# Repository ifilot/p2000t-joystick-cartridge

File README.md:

# P2000T Joystick Cartridge for SLOT2

This cartridge enables the use of Atari 2600-style joysticks with the P2000T by
emulating keyboard inputs. It uses an EEPROM and a few logic chips to translate
joystick button presses into keystrokes, seamlessly integrating with the
P2000T's keyboard polling process.

> [!TIP]
> Download a copy of the EEPROM binary [via this link](https://github.com/ifilot/p2000t-joystick-cartridge/releases/download/nightly/joystick_eeprom.bin).

## PCB

## Working

The P2000T features a matrix keyboard design, where each key is positioned at the intersection of a specific row and column. The rows are connected to the address pins, while the columns are connected to the data pins. The keyboard matrix consists of 10 rows and 8 columns.

## Keyboard Polling Process

To poll the keyboard, the P2000T employs a two-step process:

1. **Initialize Rows**: The P2000T writes a `1` to the `BIT6` position of I/O
   port `0x10`, which ties all rows to ground (GND).
2. **Detect Key Presses**: The P2000T then reads from I/O port `0x00`. If at
   least one key is pressed, the read value will differ from `0xFF`.

If a key press is detected, the P2000T proceeds with an additional step:

3. **Detect specific key**: Each row is sequentially pulled down by reading from
   I/O ports `0x00` to `0x0A`. A zero-bit received during any of these read
   operations indicates the presence of a key press. The corresponding key is
   mapped to a specific keystroke based on its position in the matrix.

The described process is emulated using a single EEPROM and a few logic chips.
The EEPROM’s address pins are connected to both the joystick buttons and the
lower address bus used by the P2000T during the keyboard polling process. To
detect the polling of the lines, a 74HC138 decoder is used. This decoder latches
the D6 pin to capture the first phase of the keyboard polling process. During
this phase, if any joystick button is pressed, the EEPROM generates the same
output as if a key on the keyboard had been pressed. In the second phase, the
EEPROM continues the emulation process. However, it now produces the output
precisely when the corresponding row in the keyboard matrix is pulled low.

The use of an EEPROM makes this process fully programmable, allowing the user to
create any desired joystick-to-keyboard mapping. With 10 joystick buttons (5 per
joystick across 2 ports), only 32 KiB of EEPROM memory is required to store the
mappings. Since even the smallest SST39SF0x0-type EEPROM has a capacity of 128
KiB, a single chip can accommodate up to four different joystick/keyboard
mappings. To enable users to select their preferred mapping, a DIP switch is
included, allowing easy switching between the stored configurations.

### Schematic

[Download schematic](pcb/p2000t-joystick-slot2-eeprom/p2000t-joystick-slot2-eeprom.pdf)

## Programming the EEPROM

To generate the data for the EEPROM, you can use [this
script](scripts/eeprom.py). The data can be written to the EEPROM using, for
example, [this hardware solution](https://github.com/ifilot/pico-sst39sf0x0-programmer).

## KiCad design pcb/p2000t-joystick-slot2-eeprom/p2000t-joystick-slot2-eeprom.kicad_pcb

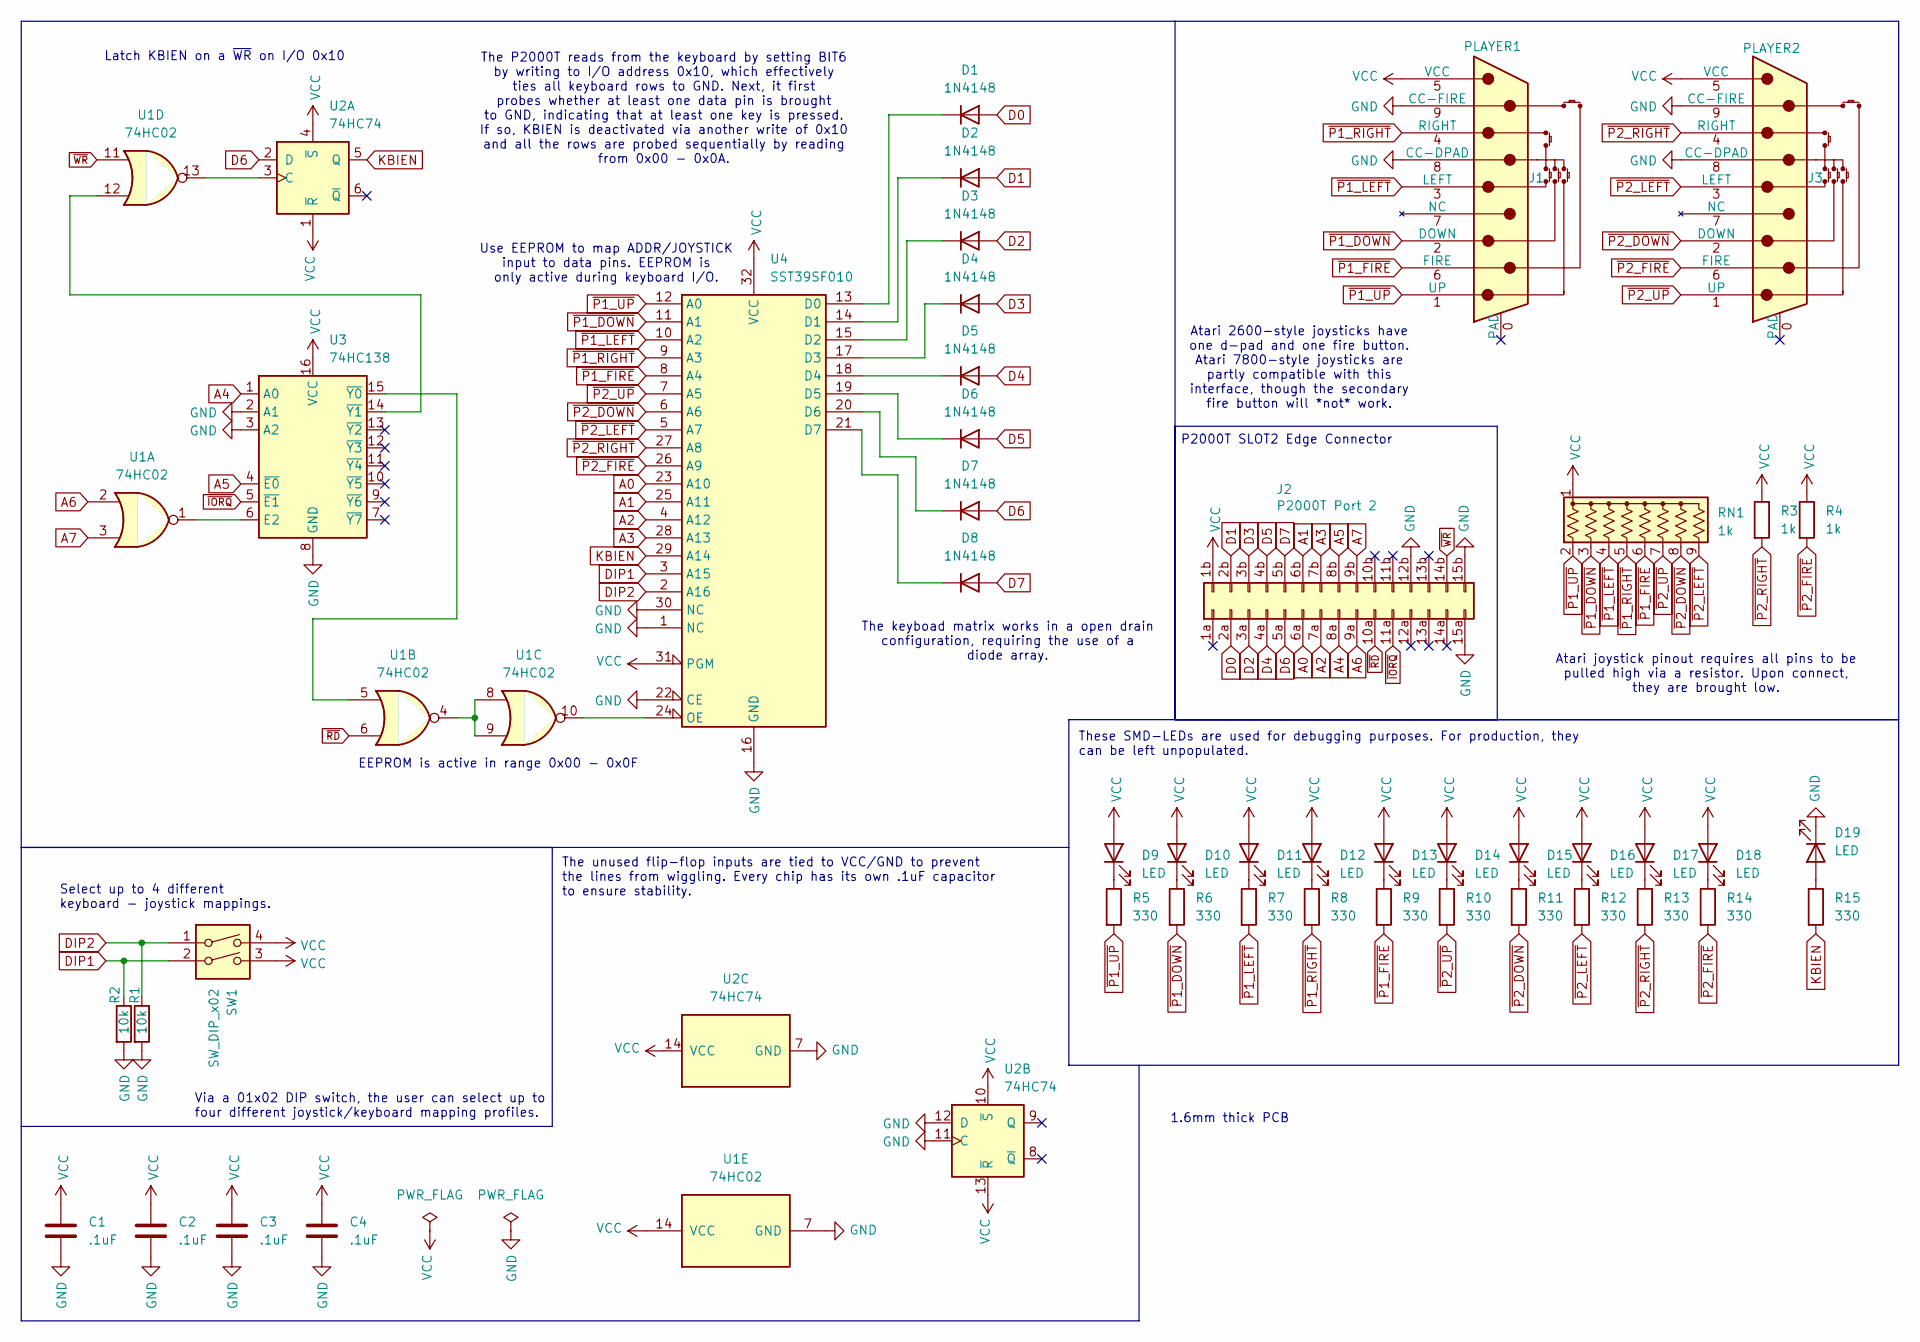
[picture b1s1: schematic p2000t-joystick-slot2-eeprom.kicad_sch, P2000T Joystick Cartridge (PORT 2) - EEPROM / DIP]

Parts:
C1, C2, C3, C4: .1uF; C_Disc_D5.0mm_W2.5mm_P5.00mm
D1, D2, D3, D4, D5, D6, D7, D8: 1N4148; D_DO-35_SOD27_P7.62mm_Horizontal
D9, D10, D11, D12, D13, D14, D15, D16, D17, D18, D19: LED; LED_0805_2012Metric_Pad1.15x1.40mm_HandSolder
J1: PLAYER1; DSUB-9_Male_Horizontal_P2.77x2.84mm_EdgePinOffset4.94mm_Hou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
J2: P2000T Port 2; p2000t_cartridge_edge
J3: PLAYER2; DSUB-9_Male_Horizontal_P2.77x2.84mm_EdgePinOffset4.94mm_Hou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
R1, R2: 10k; R_Axial_DIN0207_L6.3mm_D2.5mm_P7.62mm_Horizontal
R3, R4: 1k; R_Axial_DIN0207_L6.3mm_D2.5mm_P7.62mm_Horizontal
R5, R6, R7, R8, R9, R10, R11, R12, R13, R14, R15: 330; R_0805_2012Metric_Pad1.20x1.40mm_HandSolder
RN1: 1k; R_Array_SIP9
SW1: SW_DIP_x02; SW_DIP_SPSTx02_Slide_9.78x7.26mm_W7.62mm_P2.54mm
U1: 74HC02; DIP-14_W7.62mm_Socket
U2: 74HC74; DIP-14_W7.62mm_Socket
U3: 74HC138; DIP-16_W7.62mm_Socket
U4: SST39SF010; PLCC-32_THT-Socket

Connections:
A0: J2.6a, U4.23 (A10)
A1: J2.6b, U4.25 (A11)
A2: J2.7a, U4.4 (A12)
A3: J2.7b, U4.28 (A13)
A4: J2.8a, U3.1 (A0)
A5: J2.8b, U3.4 (~E0)
A6: J2.9a, U1.2
A7: J2.9b, U1.3
D0: D1.2 (A), J2.2a
D1: D2.2 (A), J2.2b
D2: D3.2 (A), J2.3a
D3: D4.2 (A), J2.3b
D4: D5.2 (A), J2.4a
D5: D6.2 (A), J2.4b
D6: D7.2 (A), J2.5a, U2.2 (D)
D7: D8.2 (A), J2.5b
DIP1: R2.1, SW1.2, U4.3 (A15)
DIP2: R1.1, SW1.1, U4.2 (A16)
GND: C1.2, C2.2, C3.2, C4.2, D19.1 (K), J1.8 (CC-DPAD), J1.9 (CC-FIRE), J2.12b, J2.15a, J2.15b, J3.8 (CC-DPAD), J3.9 (CC-FIRE), R1.2, R2.2, U1.7 (GND), U2.7 (GND), U2.11 (C), U2.12 (D), U3.2 (A1), U3.3 (A2), U3.8 (GND), U4.1 (NC), U4.16 (GND), U4.22 (CE), U4.30 (NC)
KBIEN: R15.2, U2.5 (Q), U4.29 (A14)
unnamed: D1.1 (K), U4.13 (D0)
unnamed: D2.1 (K), U4.14 (D1)
unnamed: D3.1 (K), U4.15 (D2)
unnamed: D4.1 (K), U4.17 (D3)
unnamed: D5.1 (K), U4.18 (D4)
unnamed: D6.1 (K), U4.19 (D5)
unnamed: D7.1 (K), U4.20 (D6)
unnamed: D8.1 (K), U4.21 (D7)
unnamed: D9.1 (K), R5.1
unnamed: D10.1 (K), R6.1
unnamed: D11.1 (K), R7.1
unnamed: D12.1 (K), R8.1
unnamed: D13.1 (K), R9.1
unnamed: D14.1 (K), R10.1
unnamed: D15.1 (K), R11.1
unnamed: D16.1 (K), R12.1
unnamed: D17.1 (K), R13.1
unnamed: D18.1 (K), R14.1
unnamed: D19.2 (A), R15.1
unnamed: U1.4, U1.8, U1.9
unnamed: U1.13, U2.3 (C)
unnamed: U1.1, U3.6 (E2)
unnamed: U1.5, U3.15 (~Y0)
unnamed: U1.12, U3.14 (~Y1)
unnamed: U1.10, U4.24 (OE)
VCC: C1.1, C2.1, C3.1, C4.1, D9.2 (A), D10.2 (A), D11.2 (A), D12.2 (A), D13.2 (A), D14.2 (A), D15.2 (A), D16.2 (A), D17.2 (A), D18.2 (A), J1.5 (VCC), J2.1b, J3.5 (VCC), R3.1, R4.1, RN1.1 (common), SW1.3, SW1.4, U1.14 (VCC), U2.1 (~R), U2.4 (~S), U2.10 (~S), U2.13 (~R), U2.14 (VCC), U3.16 (VCC), U4.31 (PGM), U4.32 (VCC)
~IORQ: J2.11a, U3.5 (~E1)
~P1_DOWN: J1.2 (DOWN), R6.2, RN1.3 (R2), U4.11 (A1)
~P1_FIRE: J1.6 (FIRE), R9.2, RN1.6 (R5), U4.8 (A4)
~P1_LEFT: J1.3 (LEFT), R7.2, RN1.4 (R3), U4.10 (A2)
~P1_RIGHT: J1.4 (RIGHT), R8.2, RN1.5 (R4), U4.9 (A3)
~P1_UP: J1.1 (UP), R5.2, RN1.2 (R1), U4.12 (A0)
~P2_DOWN: J3.2 (DOWN), R11.2, RN1.8 (R7), U4.6 (A6)
~P2_FIRE: J3.6 (FIRE), R4.2, R14.2, U4.26 (A9)
~P2_LEFT: J3.3 (LEFT), R12.2, RN1.9 (R8), U4.5 (A7)
~P2_RIGHT: J3.4 (RIGHT), R3.2, R13.2, U4.27 (A8)
~P2_UP: J3.1 (UP), R10.2, RN1.7 (R6), U4.7 (A5)
~RD: J2.10a, U1.6
~WR: J2.14b, U1.11

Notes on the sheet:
Latch KBIEN on a ~{WR} on I/O 0x10
Atari joystick pinout requires all pins to be pulled high via a resistor. Upon connect, they are brought low.
The keyboad matrix works in a open drain configuration, requiring the use of a diode array.
Select up to 4 different keyboard - joystick mappings.
Use EEPROM to map ADDR/JOYSTICK input to data pins. EEPROM is only active during keyboard I/O.
EEPROM is active in range 0x00 - 0x0F
P2000T SLOT2 Edge Connector
The P2000T reads from the keyboard by setting BIT6 by writing to I/O address 0x10, which effectively ties all keyboard rows to GND. Next, it first probes whether at least one data pin is brought to GND, indicating that at least one key is pressed. If so, KBIEN is deactivated via another write of 0x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
These SMD-LEDs are used for debugging purposes. For production, they can be left unpopulated.
The unused flip-flop inputs are tied to VCC/GND to prevent the lines from wiggling. Every chip has its own .1uF capacitor to ensure stability.
1.6mm thick PCB
Atari 2600-style joysticks have one d-pad and one fire button. Atari 7800-style joysticks are partly compatible with this interface, though the secondary fire button will *not* work.
Via a 01x02 DIP switch, the user can select up to four different joystick/keyboard mapping profiles.

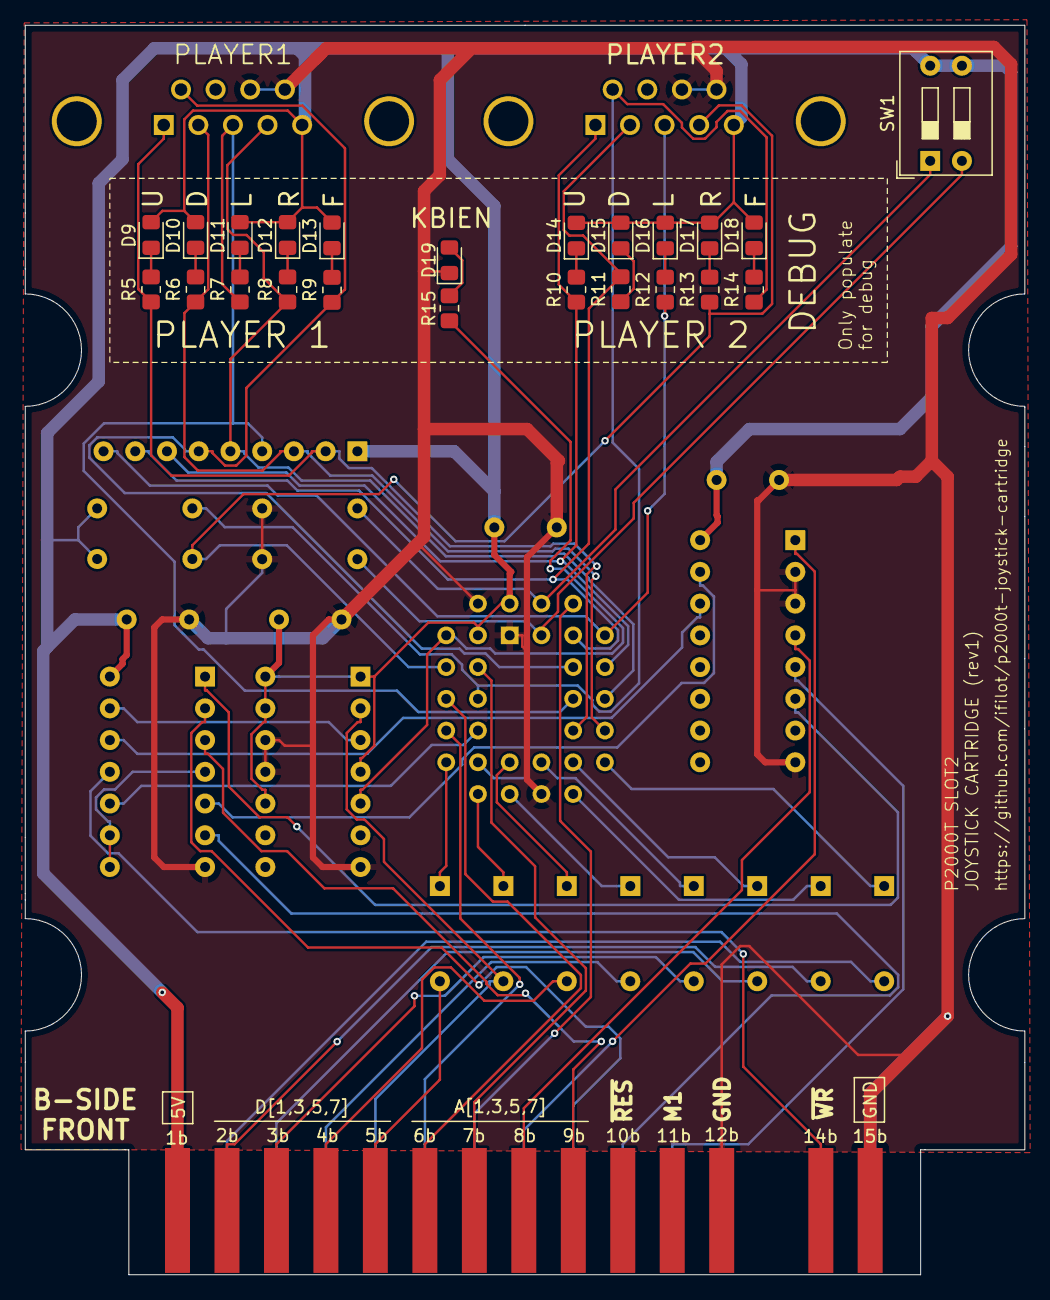
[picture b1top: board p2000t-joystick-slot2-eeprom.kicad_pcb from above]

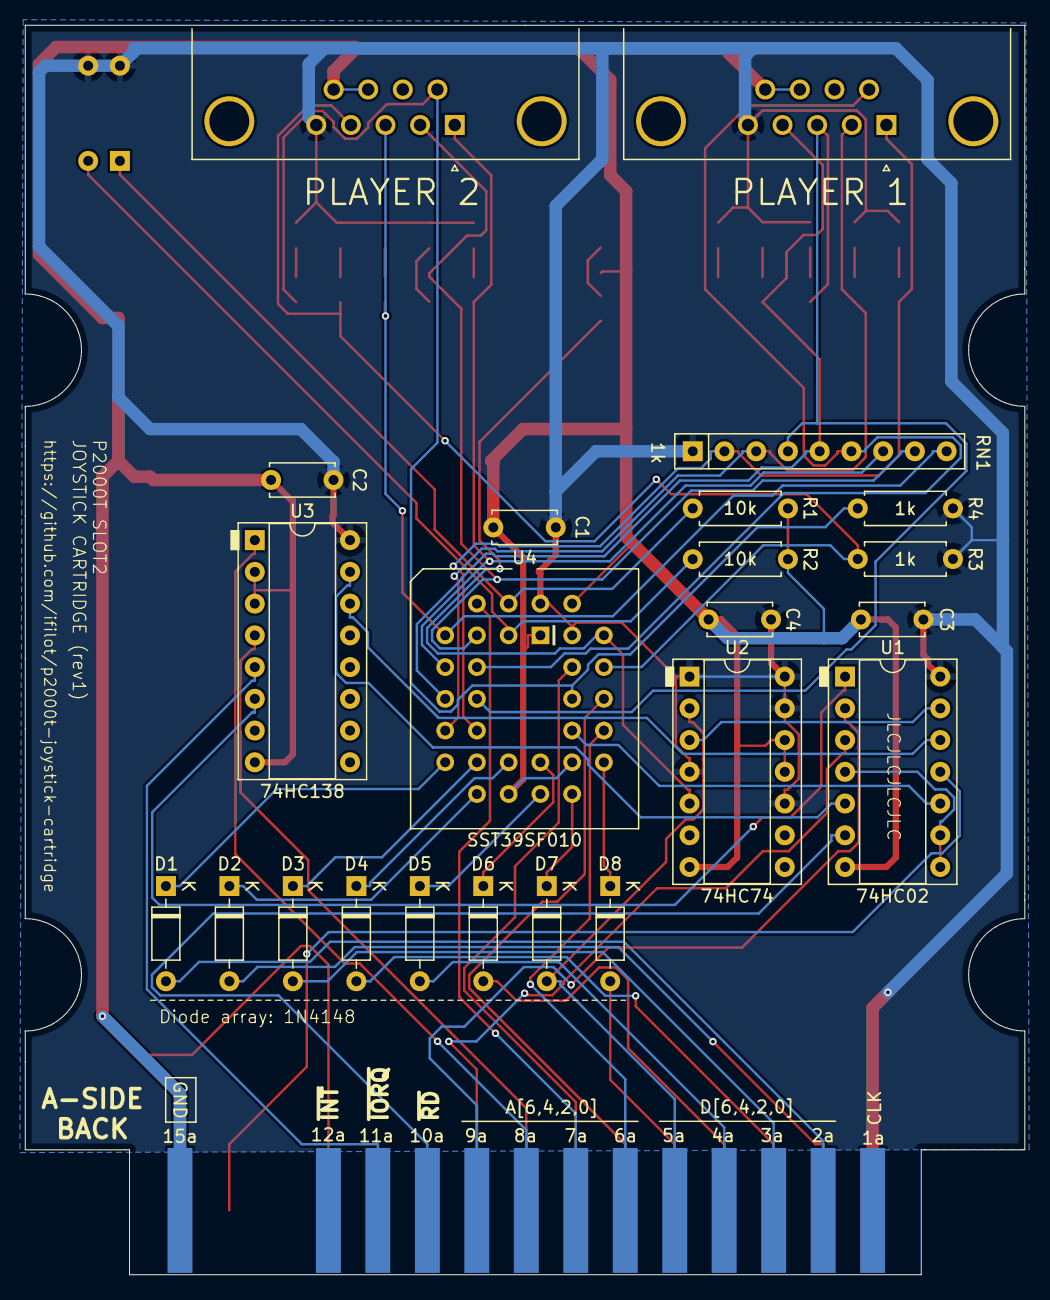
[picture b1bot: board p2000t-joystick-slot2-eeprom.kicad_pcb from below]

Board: 2 copper layers, 80.0 x 100.0 mm, 47 parts (24 on the bottom side), 59 nets.

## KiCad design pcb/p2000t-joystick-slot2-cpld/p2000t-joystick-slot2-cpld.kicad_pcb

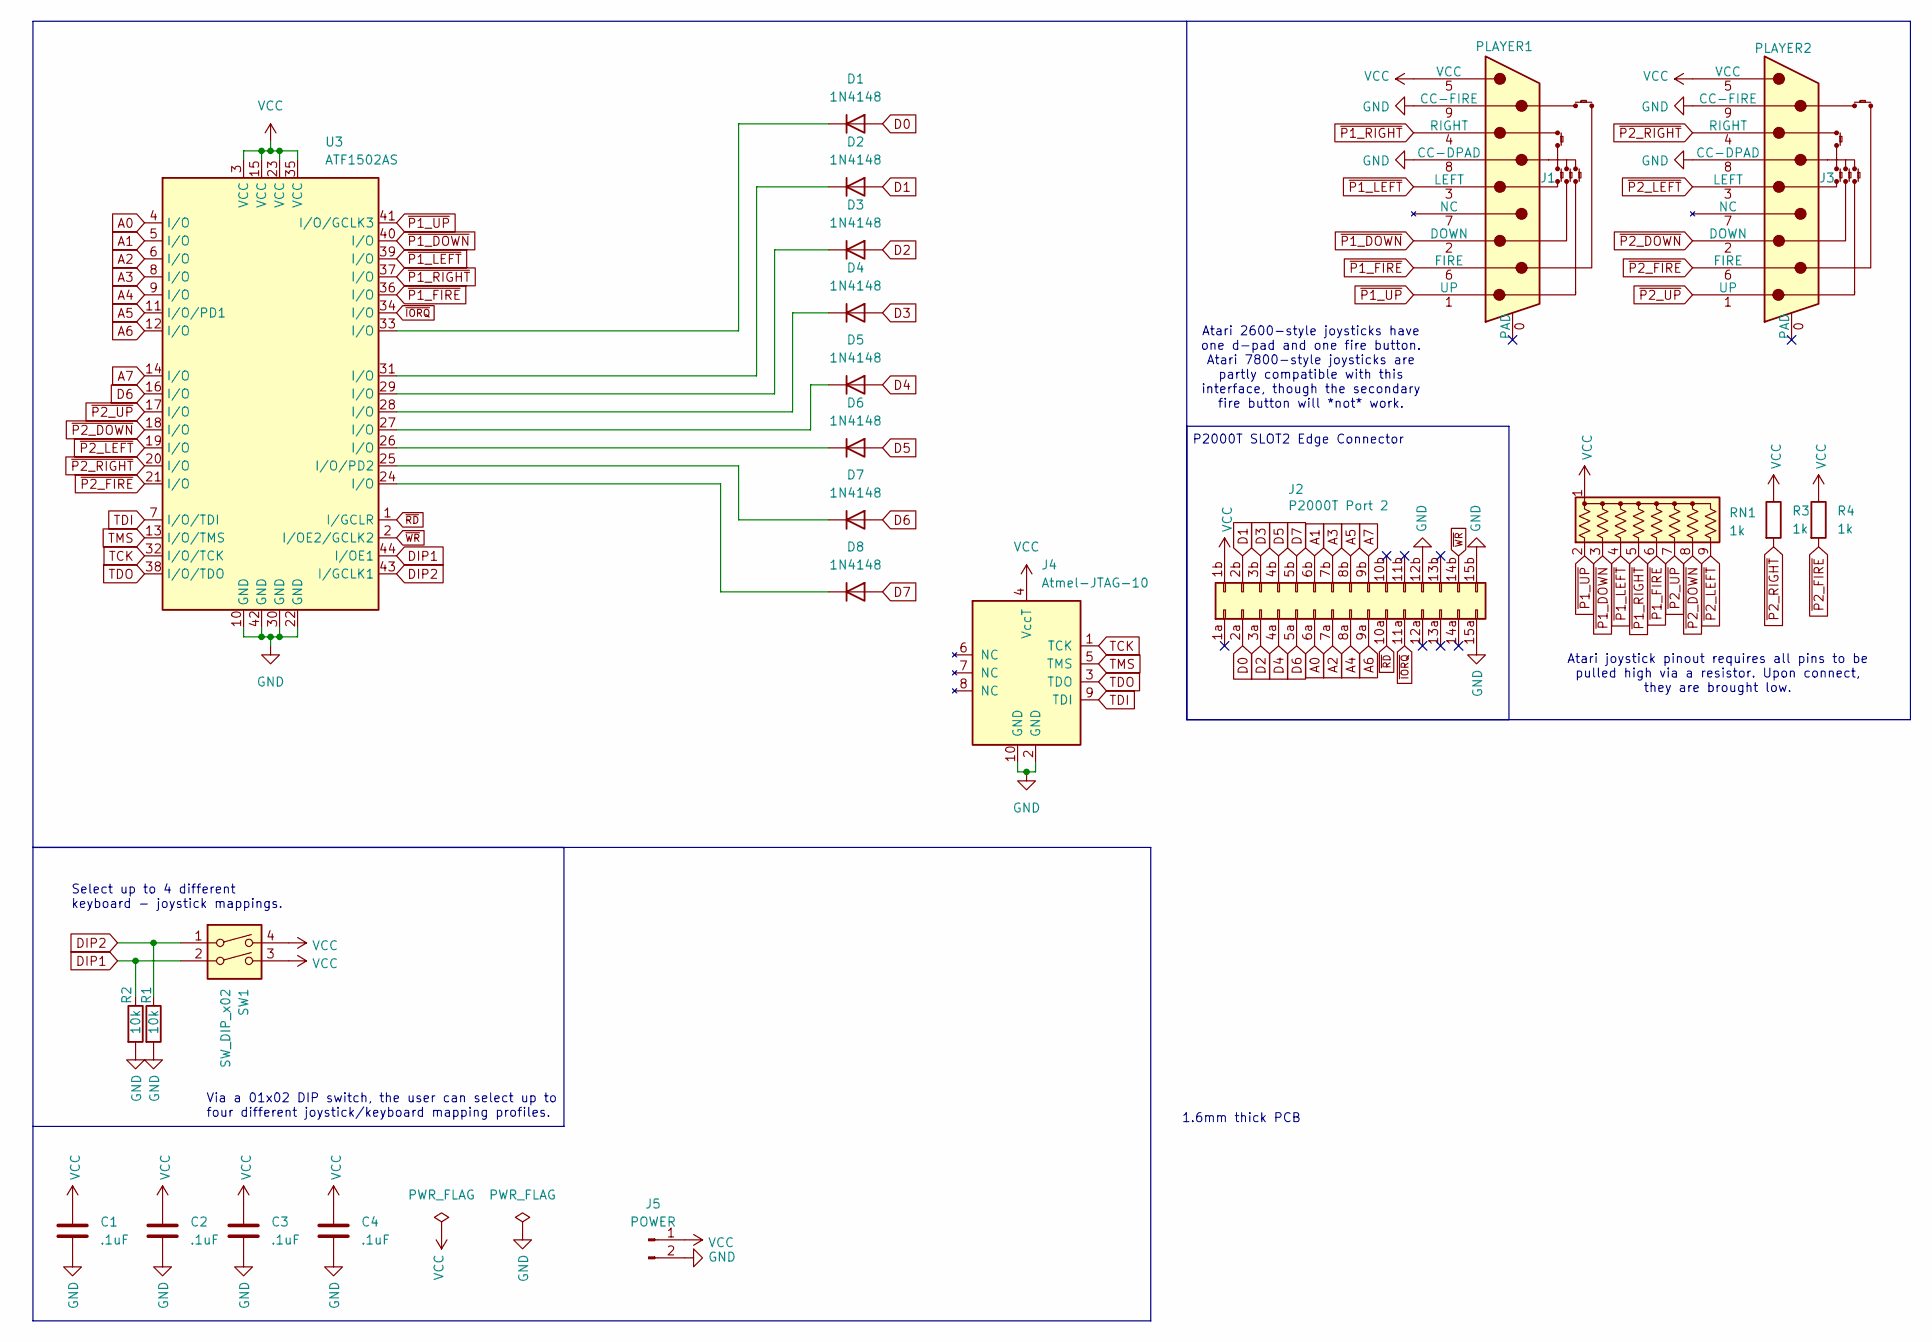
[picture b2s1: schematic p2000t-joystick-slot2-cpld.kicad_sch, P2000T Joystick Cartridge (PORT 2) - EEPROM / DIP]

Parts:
C1, C2, C3, C4: .1uF; C_Disc_D5.0mm_W2.5mm_P5.00mm
D1, D2, D3, D4, D5, D6, D7, D8: 1N4148; D_DO-35_SOD27_P7.62mm_Horizontal
J1: PLAYER1; DSUB-9_Male_Horizontal_P2.77x2.84mm_EdgePinOffset4.94mm_Hou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
J2: P2000T Port 2; p2000t_cartridge_edge
J3: PLAYER2; DSUB-9_Male_Horizontal_P2.77x2.84mm_EdgePinOffset4.94mm_Hou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
J4: Atmel-JTAG-10; IDC-Header_2x05_P2.54mm_Vertical
J5: POWER; PinSocket_1x02_P2.54mm_Vertical
R1, R2: 10k; R_Axial_DIN0207_L6.3mm_D2.5mm_P7.62mm_Horizontal
R3, R4: 1k; R_Axial_DIN0207_L6.3mm_D2.5mm_P7.62mm_Horizontal
RN1: 1k; R_Array_SIP9
SW1: SW_DIP_x02; SW_DIP_SPSTx02_Slide_9.78x7.26mm_W7.62mm_P2.54mm
U3: ATF1502AS; PLCC-44_THT-Socket

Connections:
A0: J2.6a, U3.4 (I/O)
A1: J2.6b, U3.5 (I/O)
A2: J2.7a, U3.6 (I/O)
A3: J2.7b, U3.8 (I/O)
A4: J2.8a, U3.9 (I/O)
A5: J2.8b, U3.11 (I/O/PD1)
A6: J2.9a, U3.12 (I/O)
A7: J2.9b, U3.14 (I/O)
D0: D1.2 (A), J2.2a
D1: D2.2 (A), J2.2b
D2: D3.2 (A), J2.3a
D3: D4.2 (A), J2.3b
D4: D5.2 (A), J2.4a
D5: D6.2 (A), J2.4b
D6: D7.2 (A), J2.5a, U3.16 (I/O)
D7: D8.2 (A), J2.5b
DIP1: R2.1, SW1.2, U3.44 (I/OE1)
DIP2: R1.1, SW1.1, U3.43 (I/GCLK1)
GND: C1.2, C2.2, C3.2, C4.2, J1.8 (CC-DPAD), J1.9 (CC-FIRE), J2.12b, J2.15a, J2.15b, J3.8 (CC-DPAD), J3.9 (CC-FIRE), J4.2 (GND), J4.10 (GND), J5.2, R1.2, R2.2, U3.10 (GND), U3.22 (GND), U3.30 (GND), U3.42 (GND)
unnamed: D1.1 (K), U3.33 (I/O)
unnamed: D2.1 (K), U3.31 (I/O)
unnamed: D3.1 (K), U3.29 (I/O)
unnamed: D4.1 (K), U3.28 (I/O)
unnamed: D5.1 (K), U3.27 (I/O)
unnamed: D6.1 (K), U3.26 (I/O)
unnamed: D7.1 (K), U3.25 (I/O/PD2)
unnamed: D8.1 (K), U3.24 (I/O)
TCK: J4.1 (TCK), U3.32 (I/O/TCK)
TDI: J4.9 (TDI), U3.7 (I/O/TDI)
TDO: J4.3 (TDO), U3.38 (I/O/TDO)
TMS: J4.5 (TMS), U3.13 (I/O/TMS)
VCC: C1.1, C2.1, C3.1, C4.1, J1.5 (VCC), J2.1b, J3.5 (VCC), J4.4 (VccT), J5.1, R3.1, R4.1, RN1.1 (common), SW1.3, SW1.4, U3.3 (VCC), U3.15 (VCC), U3.23 (VCC), U3.35 (VCC)
~IORQ: J2.11a, U3.34 (I/O)
~P1_DOWN: J1.2 (DOWN), RN1.3 (R2), U3.40 (I/O)
~P1_FIRE: J1.6 (FIRE), RN1.6 (R5), U3.36 (I/O)
~P1_LEFT: J1.3 (LEFT), RN1.4 (R3), U3.39 (I/O)
~P1_RIGHT: J1.4 (RIGHT), RN1.5 (R4), U3.37 (I/O)
~P1_UP: J1.1 (UP), RN1.2 (R1), U3.41 (I/O/GCLK3)
~P2_DOWN: J3.2 (DOWN), RN1.8 (R7), U3.18 (I/O)
~P2_FIRE: J3.6 (FIRE), R4.2, U3.21 (I/O)
~P2_LEFT: J3.3 (LEFT), RN1.9 (R8), U3.19 (I/O)
~P2_RIGHT: J3.4 (RIGHT), R3.2, U3.20 (I/O)
~P2_UP: J3.1 (UP), RN1.7 (R6), U3.17 (I/O)
~RD: J2.10a, U3.1 (I/GCLR)
~WR: J2.14b, U3.2 (I/OE2/GCLK2)

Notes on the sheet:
Atari joystick pinout requires all pins to be pulled high via a resistor. Upon connect, they are brought low.
Select up to 4 different keyboard - joystick mappings.
P2000T SLOT2 Edge Connector
1.6mm thick PCB
Atari 2600-style joysticks have one d-pad and one fire button. Atari 7800-style joysticks are partly compatible with this interface, though the secondary fire button will *not* work.
Via a 01x02 DIP switch, the user can select up to four different joystick/keyboard mapping profiles.

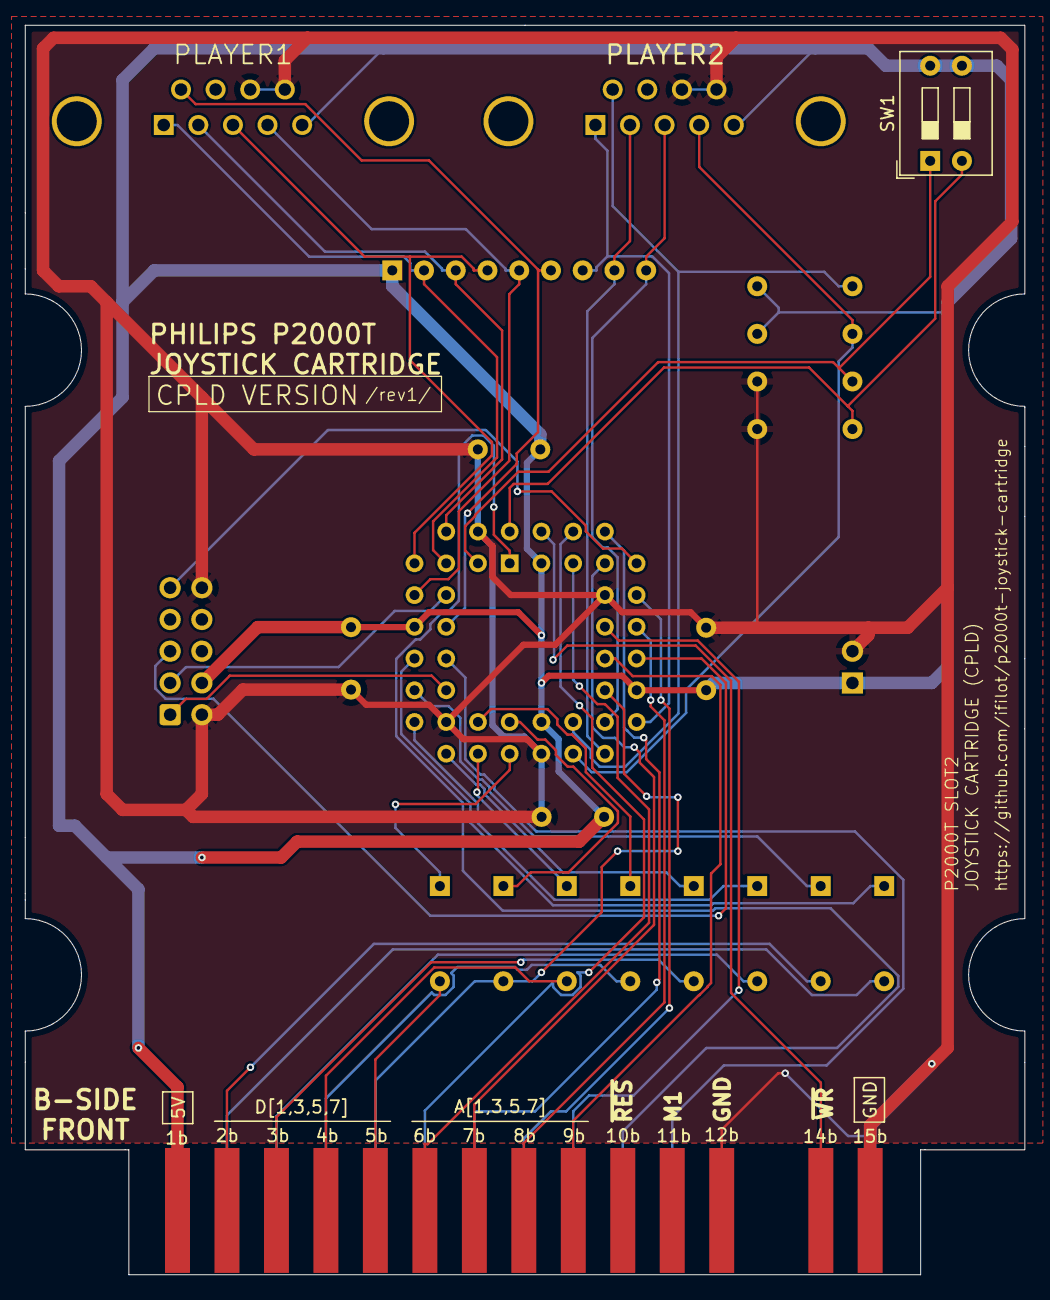
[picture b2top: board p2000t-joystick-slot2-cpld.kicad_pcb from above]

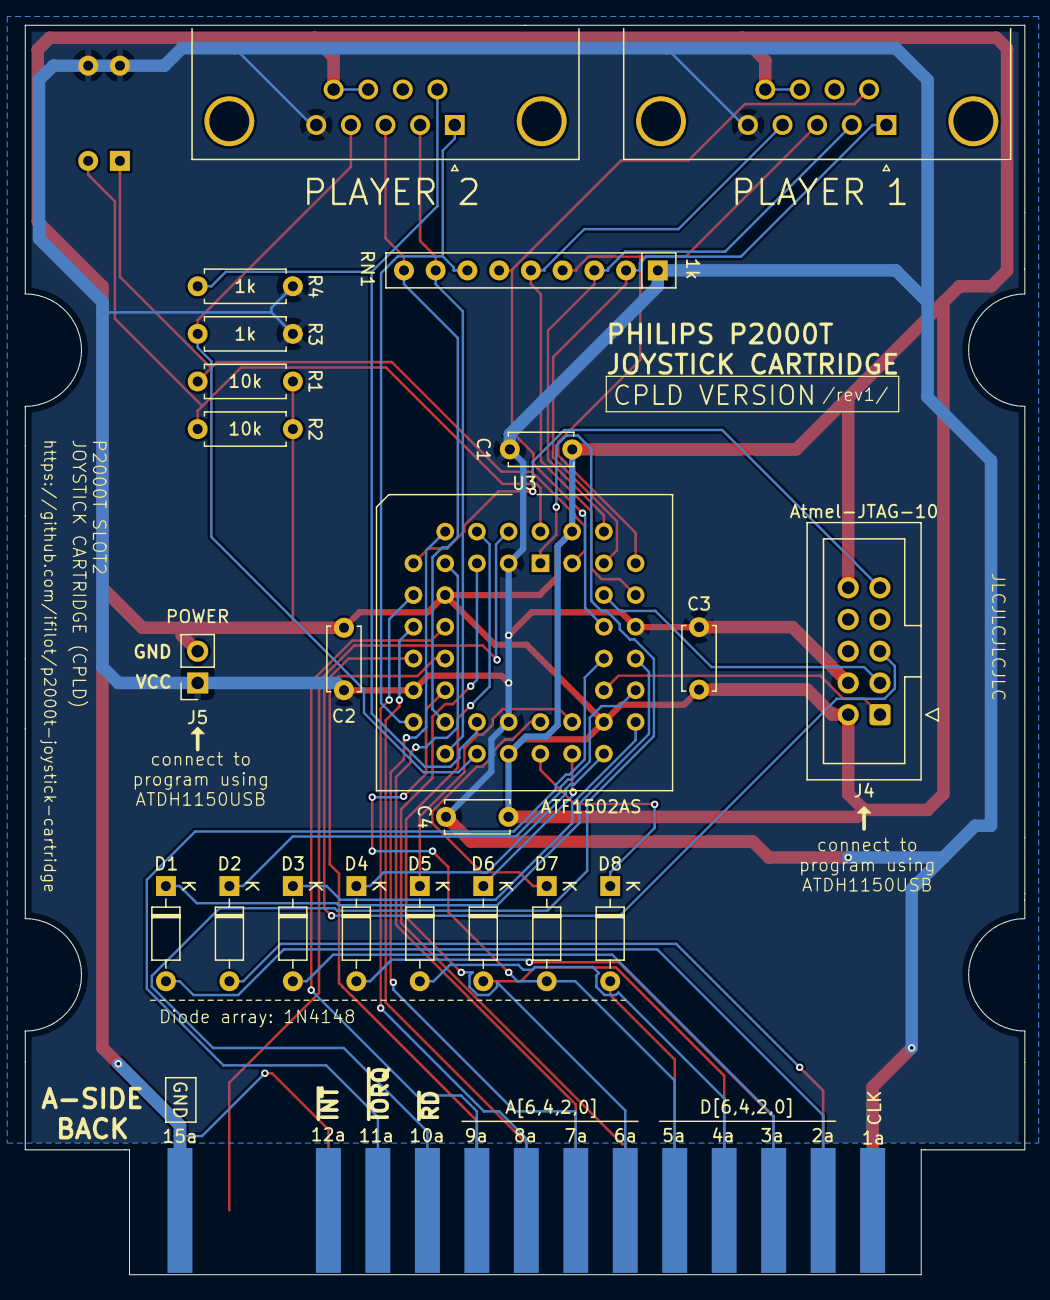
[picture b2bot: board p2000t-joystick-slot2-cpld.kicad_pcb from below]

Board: 2 copper layers, 80.0 x 100.0 mm, 24 parts (23 on the bottom side), 45 nets.

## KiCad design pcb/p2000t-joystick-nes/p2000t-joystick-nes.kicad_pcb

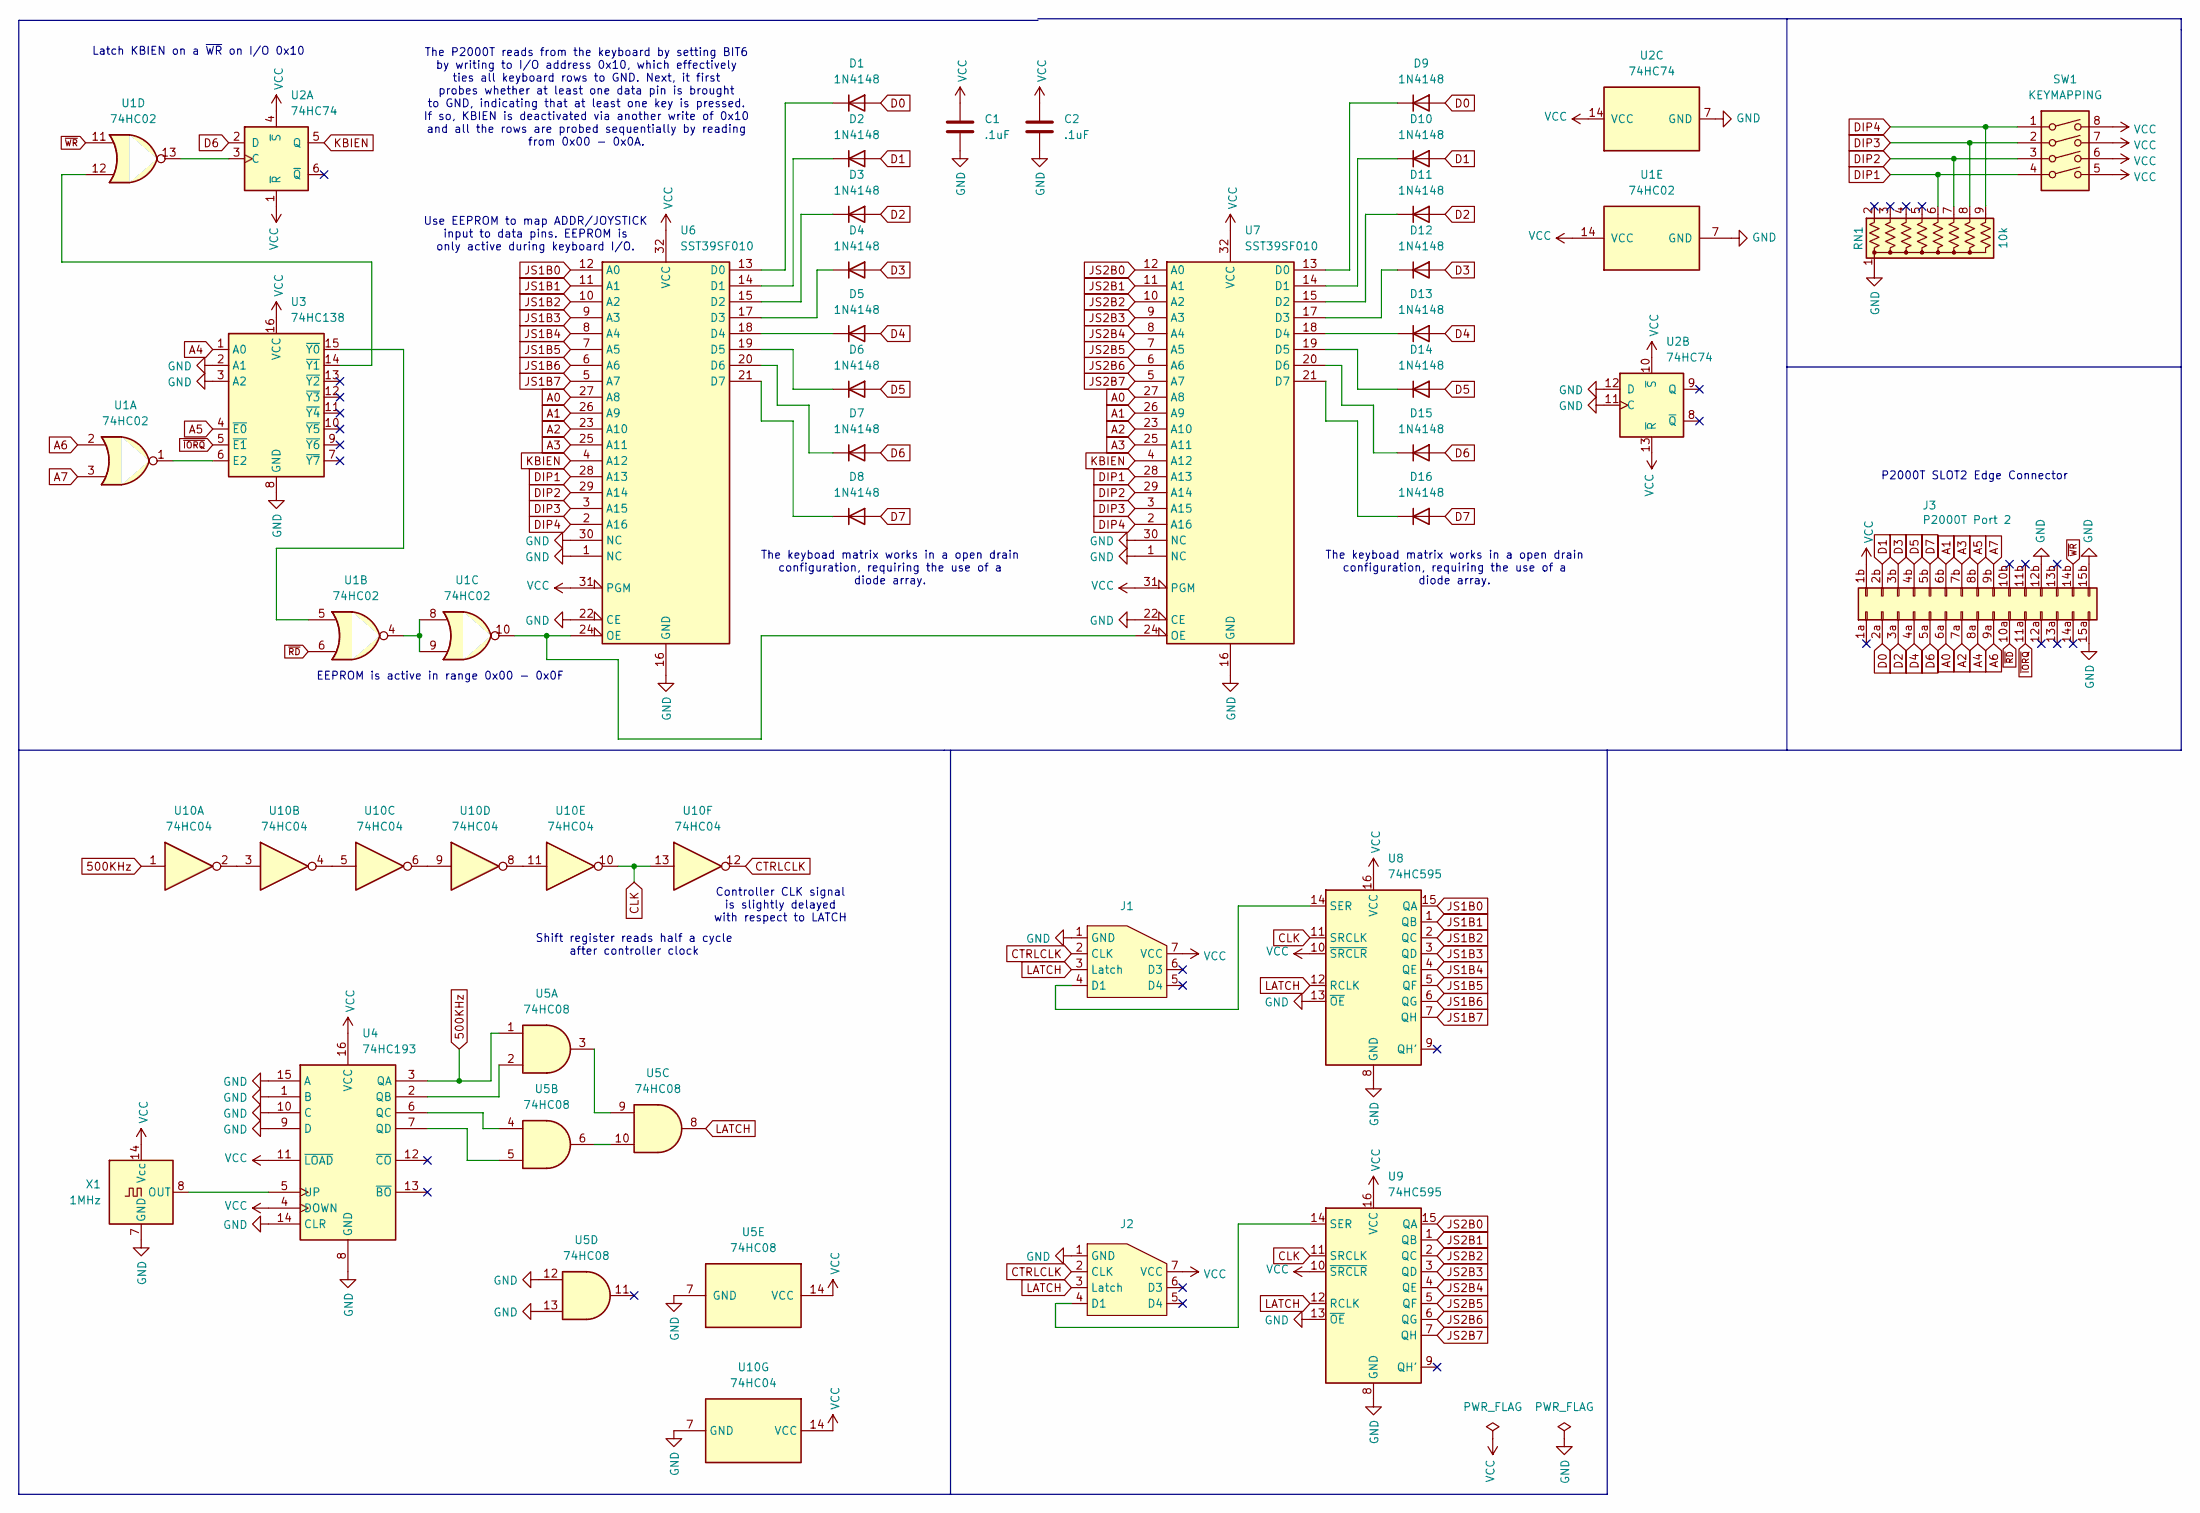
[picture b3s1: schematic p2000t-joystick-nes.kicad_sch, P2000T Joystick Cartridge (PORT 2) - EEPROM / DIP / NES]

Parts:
C1, C2: .1uF; C_Disc_D5.0mm_W2.5mm_P5.00mm
D1, D2, D3, D4, D5, D6, D7, D8, D9, D10, D11, D12, D13, D14, D15, D16: 1N4148; D_DO-35_SOD27_P7.62mm_Horizontal
J1, J2: nes_controller_port
J3: P2000T Port 2; p2000t_cartridge_edge
RN1: 10k; R_Array_SIP9
SW1: KEYMAPPING; SW_DIP_SPSTx04_Slide_9.78x12.34mm_W7.62mm_P2.54mm
U1: 74HC02; DIP-14_W7.62mm_Socket
U2: 74HC74; DIP-14_W7.62mm_Socket
U3: 74HC138; DIP-16_W7.62mm_Socket
U4: 74HC193; DIP-16_W7.62mm_Socket
U5: 74HC08; DIP-14_W7.62mm_Socket
U6, U7: SST39SF010; PLCC-32_THT-Socket
U8, U9: 74HC595; DIP-16_W7.62mm_Socket
U10: 74HC04; DIP-14_W7.62mm_Socket
X1: 1MHz; Oscillator_DIP-14

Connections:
500KHz: U4.3 (QA), U5.1, U10.1
A0: J3.6a, U6.27 (A8), U7.27 (A8)
A1: J3.6b, U6.26 (A9), U7.26 (A9)
A2: J3.7a, U6.23 (A10), U7.23 (A10)
A3: J3.7b, U6.25 (A11), U7.25 (A11)
A4: J3.8a, U3.1 (A0)
A5: J3.8b, U3.4 (~E0)
A6: J3.9a, U1.2
A7: J3.9b, U1.3
CLK: U8.11 (SRCLK), U9.11 (SRCLK), U10.10, U10.13
CTRLCLK: J1.2 (CLK), J2.2 (CLK), U10.12
D0: D1.2 (A), D9.2 (A), J3.2a
D1: D2.2 (A), D10.2 (A), J3.2b
D2: D3.2 (A), D11.2 (A), J3.3a
D3: D4.2 (A), D12.2 (A), J3.3b
D4: D5.2 (A), D13.2 (A), J3.4a
D5: D6.2 (A), D14.2 (A), J3.4b
D6: D7.2 (A), D15.2 (A), J3.5a, U2.2 (D)
D7: D8.2 (A), D16.2 (A), J3.5b
DIP1: RN1.6 (R5), SW1.4, U6.28 (A13), U7.28 (A13)
DIP2: RN1.7 (R6), SW1.3, U6.29 (A14), U7.29 (A14)
DIP3: RN1.8 (R7), SW1.2, U6.3 (A15), U7.3 (A15)
DIP4: RN1.9 (R8), SW1.1, U6.2 (A16), U7.2 (A16)
GND: C1.2, C2.2, J1.1 (GND), J2.1 (GND), J3.12b, J3.15a, J3.15b, RN1.1 (common), U1.7 (GND), U2.7 (GND), U2.11 (C), U2.12 (D), U3.2 (A1), U3.3 (A2), U3.8 (GND), U4.1 (B), U4.8 (GND), U4.9 (D), U4.10 (C), U4.14 (CLR), U4.15 (A), U5.7 (GND), U5.12, U5.13, U6.1 (NC), U6.16 (GND), U6.22 (CE), U6.30 (NC), U7.1 (NC), U7.16 (GND), U7.22 (CE), U7.30 (NC), U8.8 (GND), U8.13 (~OE), U9.8 (GND), U9.13 (~OE), U10.7 (GND), X1.7 (GND)
JS1B0: U6.12 (A0), U8.15 (QA)
JS1B1: U6.11 (A1), U8.1 (QB)
JS1B2: U6.10 (A2), U8.2 (QC)
JS1B3: U6.9 (A3), U8.3 (QD)
JS1B4: U6.8 (A4), U8.4 (QE)
JS1B5: U6.7 (A5), U8.5 (QF)
JS1B6: U6.6 (A6), U8.6 (QG)
JS1B7: U6.5 (A7), U8.7 (QH)
JS2B0: U7.12 (A0), U9.15 (QA)
JS2B1: U7.11 (A1), U9.1 (QB)
JS2B2: U7.10 (A2), U9.2 (QC)
JS2B3: U7.9 (A3), U9.3 (QD)
JS2B4: U7.8 (A4), U9.4 (QE)
JS2B5: U7.7 (A5), U9.5 (QF)
JS2B6: U7.6 (A6), U9.6 (QG)
JS2B7: U7.5 (A7), U9.7 (QH)
KBIEN: U2.5 (Q), U6.4 (A12), U7.4 (A12)
LATCH: J1.3 (Latch), J2.3 (Latch), U5.8, U8.12 (RCLK), U9.12 (RCLK)
unnamed: D1.1 (K), U6.13 (D0)
unnamed: D2.1 (K), U6.14 (D1)
unnamed: D3.1 (K), U6.15 (D2)
unnamed: D4.1 (K), U6.17 (D3)
unnamed: D5.1 (K), U6.18 (D4)
unnamed: D6.1 (K), U6.19 (D5)
unnamed: D7.1 (K), U6.20 (D6)
unnamed: D8.1 (K), U6.21 (D7)
unnamed: D9.1 (K), U7.13 (D0)
unnamed: D10.1 (K), U7.14 (D1)
unnamed: D11.1 (K), U7.15 (D2)
unnamed: D12.1 (K), U7.17 (D3)
unnamed: D13.1 (K), U7.18 (D4)
unnamed: D14.1 (K), U7.19 (D5)
unnamed: D15.1 (K), U7.20 (D6)
unnamed: D16.1 (K), U7.21 (D7)
unnamed: J1.4 (D1), U8.14 (SER)
unnamed: J2.4 (D1), U9.14 (SER)
unnamed: U1.4, U1.8, U1.9
unnamed: U1.13, U2.3 (C)
unnamed: U1.1, U3.6 (E2)
unnamed: U1.5, U3.15 (~Y0)
unnamed: U1.12, U3.14 (~Y1)
unnamed: U4.2 (QB), U5.2
unnamed: U4.6 (QC), U5.4
unnamed: U4.7 (QD), U5.5
unnamed: U4.5 (UP), X1.8 (OUT)
unnamed: U5.3, U5.9
unnamed: U5.6, U5.10
unnamed: U1.10, U6.24 (OE), U7.24 (OE)
unnamed: U10.2, U10.3
unnamed: U10.4, U10.5
unnamed: U10.6, U10.9
unnamed: U10.8, U10.11
VCC: C1.1, C2.1, J1.7 (VCC), J2.7 (VCC), J3.1b, SW1.5, SW1.6, SW1.7, SW1.8, U1.14 (VCC), U2.1 (~R), U2.4 (~S), U2.10 (~S), U2.13 (~R), U2.14 (VCC), U3.16 (VCC), U4.4 (DOWN), U4.11 (~LOAD), U4.16 (VCC), U5.14 (VCC), U6.31 (PGM), U6.32 (VCC), U7.31 (PGM), U7.32 (VCC), U8.10 (~SRCLR), U8.16 (VCC), U9.10 (~SRCLR), U9.16 (VCC), U10.14 (VCC), X1.14 (Vcc)
~IORQ: J3.11a, U3.5 (~E1)
~RD: J3.10a, U1.6
~WR: J3.14b, U1.11

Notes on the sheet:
Controller CLK signal is slightly delayed with respect to LATCH
Latch KBIEN on a ~{WR} on I/O 0x10
The keyboad matrix works in a open drain configuration, requiring the use of a diode array.
Shift register reads half a cycle after controller clock
Use EEPROM to map ADDR/JOYSTICK input to data pins. EEPROM is only active during keyboard I/O.
EEPROM is active in range 0x00 - 0x0F
P2000T SLOT2 Edge Connector
The P2000T reads from the keyboard by setting BIT6 by writing to I/O address 0x10, which effectively ties all keyboard rows to GND. Next, it first probes whether at least one data pin is brought to GND, indicating that at least one key is pressed. If so, KBIEN is deactivated via another write of 0x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

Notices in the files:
README.md:
License: GPL v3
License: CC-BY-SA v4
